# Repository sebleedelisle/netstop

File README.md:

# netstop
All files for my netstop system that combines network and interlock cables for laser control. 

Currently only contains files to make a simple combiner / splitter. 

Share-alike license : 
https://creativecommons.org/licenses/by-sa/4.0/

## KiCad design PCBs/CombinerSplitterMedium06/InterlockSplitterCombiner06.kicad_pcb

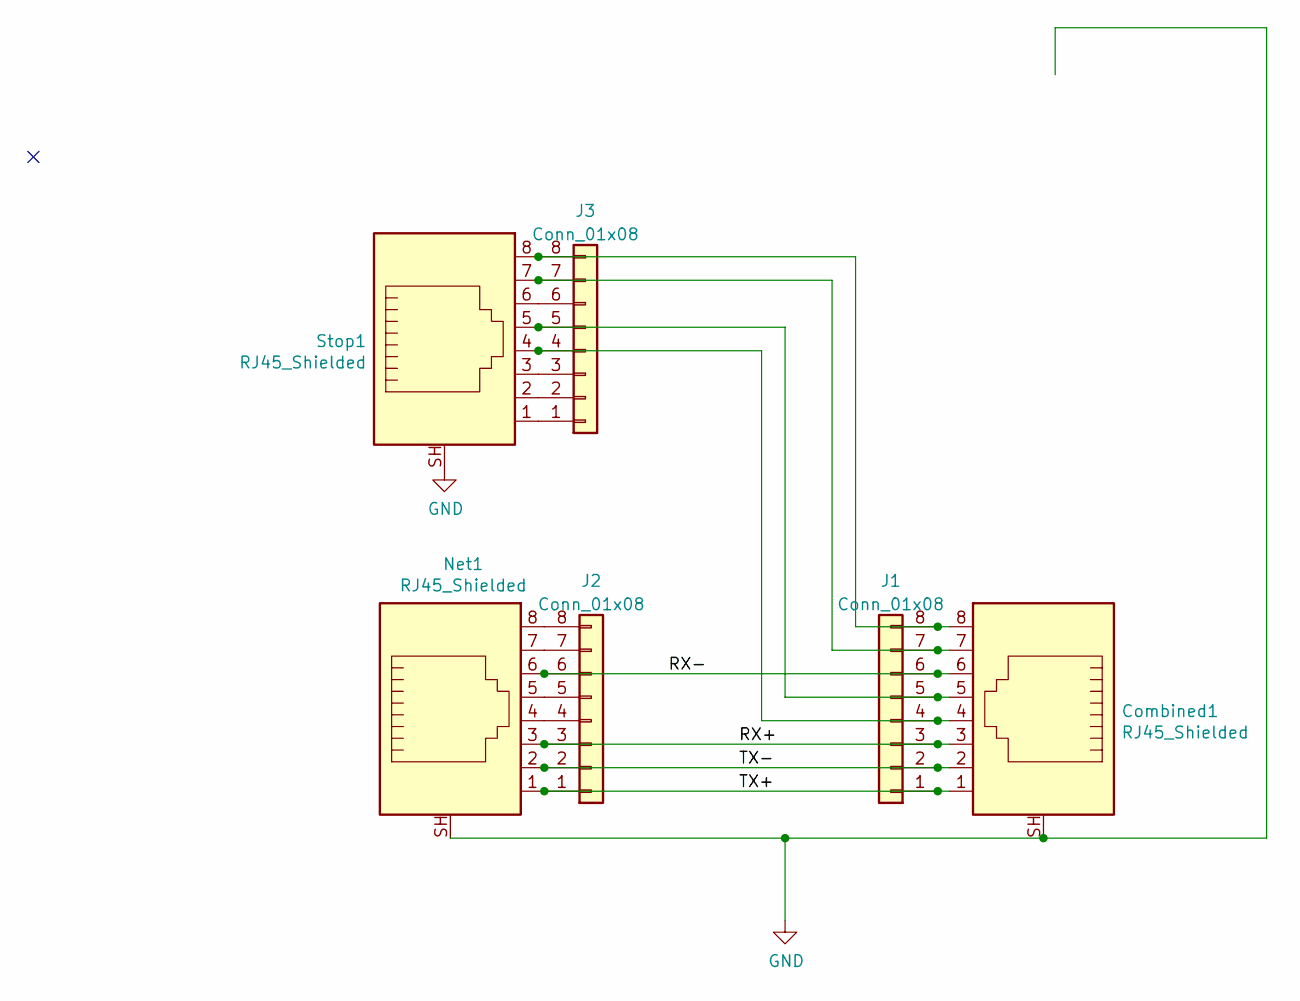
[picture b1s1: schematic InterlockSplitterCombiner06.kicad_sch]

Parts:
Combined1: RJ45_Shielded; RJ45_Multiple3
J1, J2, J3: Conn_01x08
Net1: RJ45_Shielded; RJ45_Multiple3
Stop1: RJ45_Shielded; RJ45_Multiple3

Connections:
/RX+: Combined1.3, J1.3, J2.3, Net1.3
/RX-: Combined1.6, J1.6, J2.6, Net1.6
/TX+: Combined1.1, J1.1, J2.1, Net1.1
/TX-: Combined1.2, J1.2, J2.2, Net1.2
GND: Combined1.SH, Net1.SH, Stop1.SH
unnamed: Combined1.4, J1.4, J3.4, Stop1.4
unnamed: Combined1.5, J1.5, J3.5, Stop1.5
unnamed: Combined1.7, J1.7, J3.7, Stop1.7
unnamed: Combined1.8, J1.8, J3.8, Stop1.8
unnamed: J2.4, Net1.4
unnamed: J2.5, Net1.5
unnamed: J2.7, Net1.7
unnamed: J2.8, Net1.8
unnamed: J3.1, Stop1.1
unnamed: J3.2, Stop1.2
unnamed: J3.3, Stop1.3
unnamed: J3.6, Stop1.6

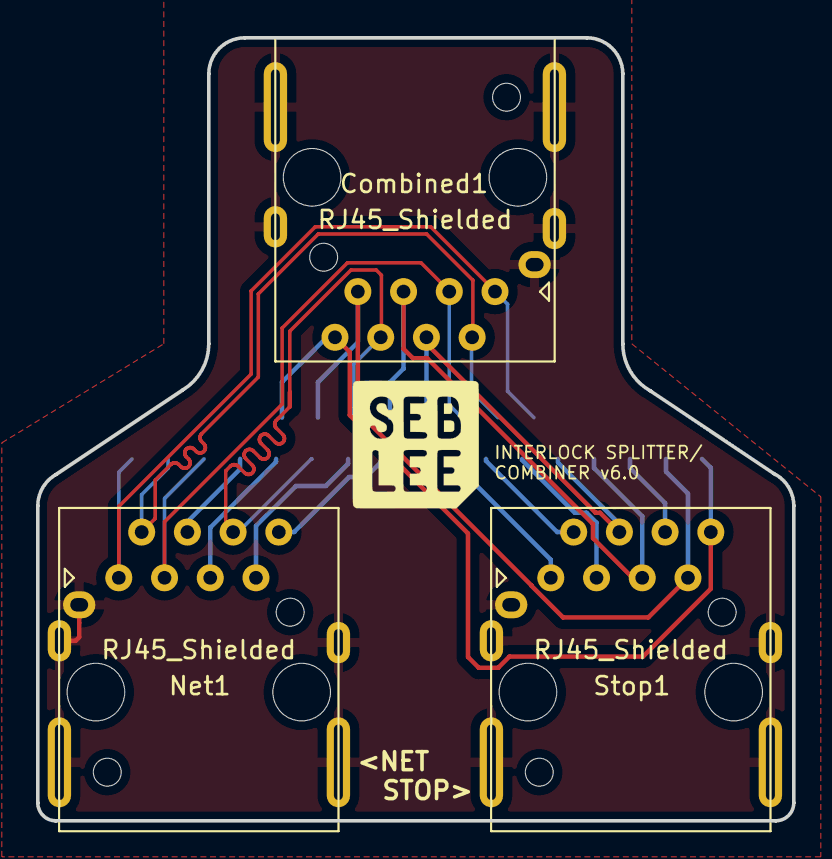
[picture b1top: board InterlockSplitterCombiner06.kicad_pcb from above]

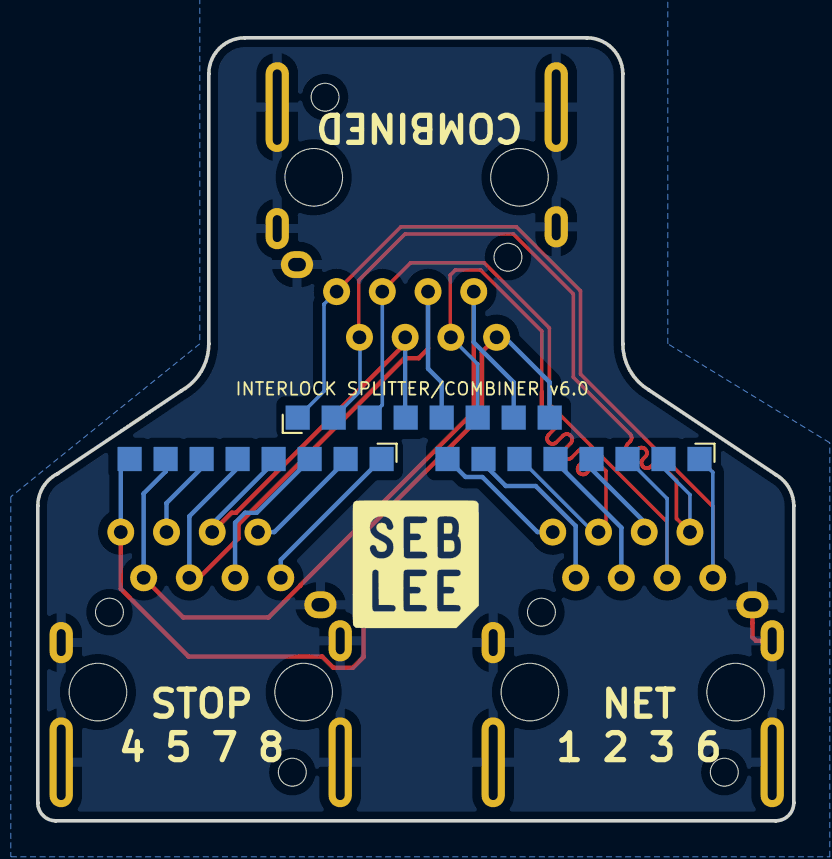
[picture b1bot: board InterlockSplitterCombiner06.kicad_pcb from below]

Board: 2 copper layers, 42.0 x 43.5 mm, 6 parts (3 on the bottom side), 17 nets.

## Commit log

2025-06-06 Committing basic splitter / combiner filess
2025-06-06 Adding pictures
2025-06-06 Add license
2025-08-16 Adding laser network adapter
2025-08-16 updated text
